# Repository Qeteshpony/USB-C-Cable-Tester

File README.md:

# USB-C Cable Tester

[Hardware Documentation](https://qeteshpony.github.io/USB-C-Cable-Tester)

Small passive device for determining the capabilities of a USB-C Cable

This helps when you have a USB-C cable and don't know which USB-Version and other features it supports. 

The tester can of course not check for any active circuitry in the cable and might not work at all with active cables but in most cases it should give you a good overview.

| LED       | Meaning   |
|:----------|:----------|
| VBUS 1-4  | One LED for each VBUS connection in the cable. Can give a hint on power capabilities |
| VGND 1-4  | One LED for each Ground connection |
| Shield    | Shows if the shielding is connected on both ends |
| USB 2.0   | Lights up when the USB2 differential pair is connected |
| USB 3.x   | One LED for each set of TX/RX pairs in the cable. If only one is lit, USB3.2 will not work |
| CC        | One of these must be connected, the other should not be. A dim LED *can* be a hint for an active cable |
| SBU       | SideBand Use (See [USB Type-C Spec R2.0, chapter 4.3](https://www.usb.org/sites/default/files/USB%20Type-C%20Spec%20R2.0%20-%20August%202019.pdf)) - Used for alternate modes like audio and video connections |

The PCB is designed with production by JLCPCB in mind and all parts but the USB-Connectors are from their basic parts library. I strongly suggest getting these assembled since soldering the USB connectors by hand is not easy.

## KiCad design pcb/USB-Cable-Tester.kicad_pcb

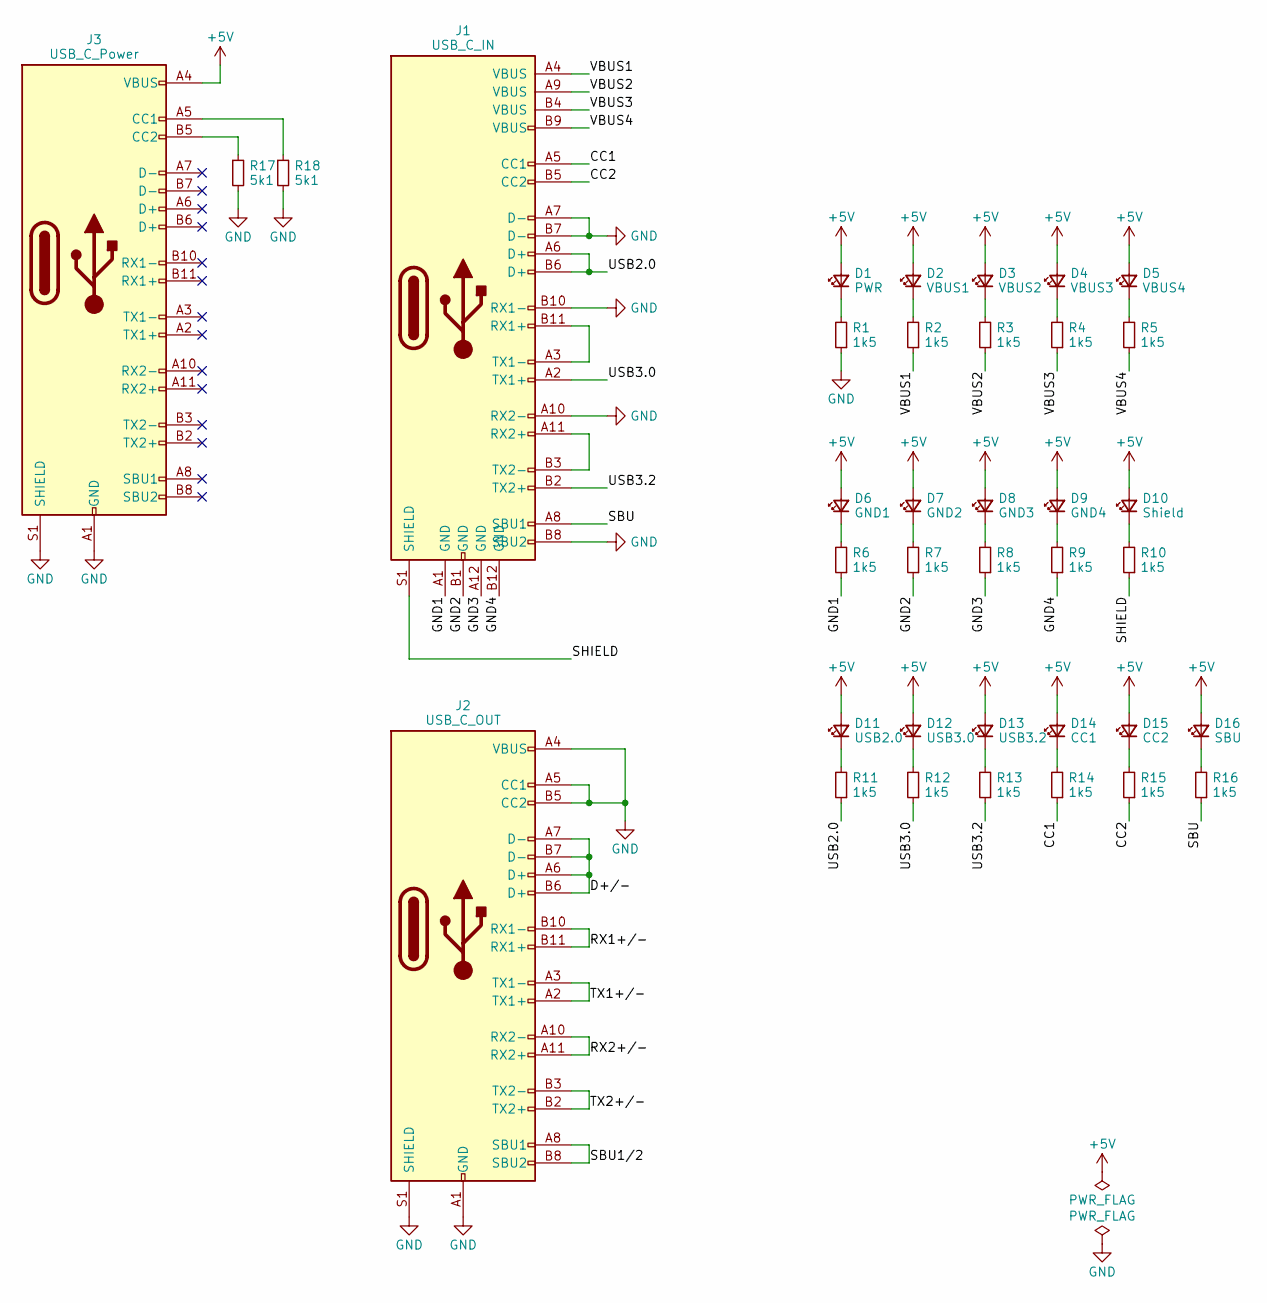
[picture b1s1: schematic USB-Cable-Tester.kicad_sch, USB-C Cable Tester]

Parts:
D1: PWR; LED_0603_1608Metric; LCSC C2286
D2: VBUS1; LED_0603_1608Metric; LCSC C2286
D3: VBUS2; LED_0603_1608Metric; LCSC C2286
D4: VBUS3; LED_0603_1608Metric; LCSC C2286
D5: VBUS4; LED_0603_1608Metric; LCSC C2286
D6: GND1; LED_0603_1608Metric; LCSC C2286
D7: GND2; LED_0603_1608Metric; LCSC C2286
D8: GND3; LED_0603_1608Metric; LCSC C2286
D9: GND4; LED_0603_1608Metric; LCSC C2286
D10: Shield; LED_0603_1608Metric; LCSC C2286
D11: USB2.0; LED_0603_1608Metric; LCSC C2286
D12: USB3.0; LED_0603_1608Metric; LCSC C2286
D13: USB3.2; LED_0603_1608Metric; LCSC C2286
D14: CC1; LED_0603_1608Metric; LCSC C2286
D15: CC2; LED_0603_1608Metric; LCSC C2286
D16: SBU; LED_0603_1608Metric; LCSC C2286
J1: USB_C_IN; USB_C_Receptacle_GT-USB-7028C; LCSC C3001280
J2: USB_C_OUT; USB_C_Receptacle_GT-USB-7028C; LCSC C3001280
J3: USB_C_Power; USB_C_Receptacle_GT-USB-7028C; LCSC C3001280
R1, R2, R3, R4, R5, R6, R7, R8, R9, R10, R11, R12, R13, R14, R15, R16: 1k5; R_0603_1608Metric; LCSC C22843
R17, R18: 5k1; R_0603_1608Metric; LCSC C23186

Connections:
+5V: D1.2 (A), D2.2 (A), D3.2 (A), D4.2 (A), D5.2 (A), D6.2 (A), D7.2 (A), D8.2 (A), D9.2 (A), D10.2 (A), D11.2 (A), D12.2 (A), D13.2 (A), D14.2 (A), D15.2 (A), D16.2 (A), J3.A4 (VBUS), J3.A9 (VBUS), J3.B4 (VBUS), J3.B9 (VBUS)
/CC1: J1.A5 (CC1), R14.1
/CC2: J1.B5 (CC2), R15.1
/D+/-: J2.A6 (D+), J2.A7 (D-), J2.B6 (D+), J2.B7 (D-)
/GND1: J1.A1 (GND), R6.1
/GND2: J1.B1 (GND), R7.1
/GND3: J1.A12 (GND), R8.1
/GND4: J1.B12 (GND), R9.1
/RX1+/-: J2.B10 (RX1-), J2.B11 (RX1+)
/RX2+/-: J2.A10 (RX2-), J2.A11 (RX2+)
/SBU: J1.A8 (SBU1), R16.1
/SBU1/2: J2.A8 (SBU1), J2.B8 (SBU2)
/SHIELD: J1.S1 (SHIELD), R10.1
/TX1+/-: J2.A2 (TX1+), J2.A3 (TX1-)
/TX2+/-: J2.B2 (TX2+), J2.B3 (TX2-)
/USB2.0: J1.A6 (D+), J1.B6 (D+), R11.1
/USB3.0: J1.A2 (TX1+), R12.1
/USB3.2: J1.B2 (TX2+), R13.1
/VBUS1: J1.A4 (VBUS), R2.1
/VBUS2: J1.A9 (VBUS), R3.1
/VBUS3: J1.B4 (VBUS), R4.1
/VBUS4: J1.B9 (VBUS), R5.1
GND: J1.A7 (D-), J1.A10 (RX2-), J1.B7 (D-), J1.B8 (SBU2), J1.B10 (RX1-), J2.A1 (GND), J2.A4 (VBUS), J2.A5 (CC1), J2.A9 (VBUS), J2.A12 (GND), J2.B1 (GND), J2.B4 (VBUS), J2.B5 (CC2), J2.B9 (VBUS), J2.B12 (GND), J2.S1 (SHIELD), J3.A1 (GND), J3.A12 (GND), J3.B1 (GND), J3.B12 (GND), J3.S1 (SHIELD), R1.1, R17.2, R18.2
unnamed: D1.1 (K), R1.2
unnamed: D2.1 (K), R2.2
unnamed: D3.1 (K), R3.2
unnamed: D4.1 (K), R4.2
unnamed: D5.1 (K), R5.2
unnamed: D6.1 (K), R6.2
unnamed: D7.1 (K), R7.2
unnamed: D8.1 (K), R8.2
unnamed: D9.1 (K), R9.2
unnamed: D10.1 (K), R10.2
unnamed: D11.1 (K), R11.2
unnamed: D12.1 (K), R12.2
unnamed: D13.1 (K), R13.2
unnamed: D14.1 (K), R14.2
unnamed: D15.1 (K), R15.2
unnamed: D16.1 (K), R16.2
unnamed: J1.A3 (TX1-), J1.B11 (RX1+)
unnamed: J1.A11 (RX2+), J1.B3 (TX2-)
unnamed: J3.A5 (CC1), R18.1
unnamed: J3.B5 (CC2), R17.1

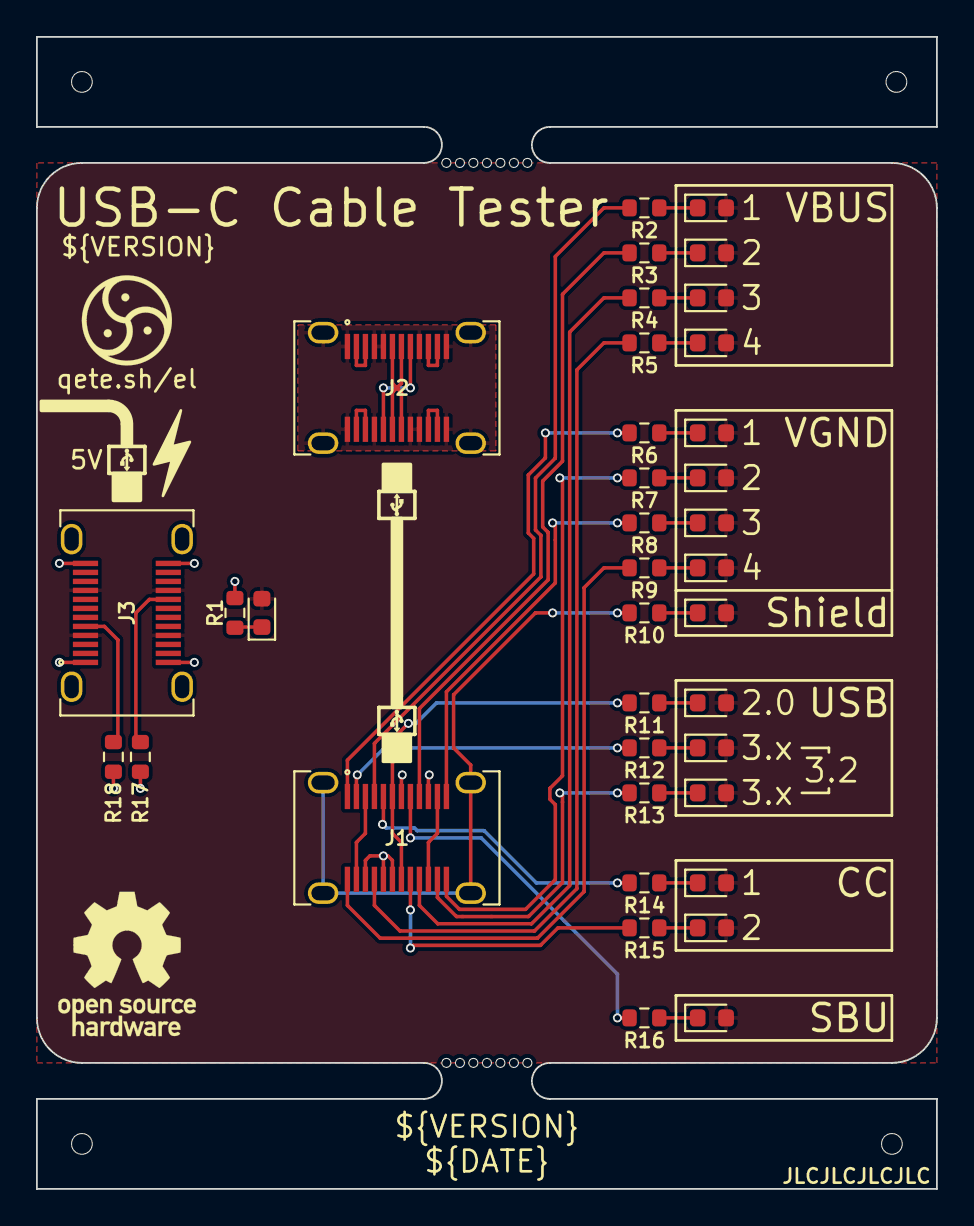
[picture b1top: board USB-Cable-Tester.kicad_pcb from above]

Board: 2 copper layers, 50.0 x 64.0 mm, 39 parts (0 on the bottom side), 43 nets.

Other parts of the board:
mouse-bite-2mm-slot, mouse-bite-2mm-slot#2: VAL**; mouse-bite-2x5mm-slot-onesided-v2

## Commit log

2023-07-28 feat: initial release
2023-07-28 chore(main): release 1.0.0
2023-07-28 docs: update links
2023-07-28 docs: update LED description
2023-07-28 docs: add link to specification for SBU
2023-07-28 style: silkscreen additions
2024-08-29 ci: remove dependency between jobs
